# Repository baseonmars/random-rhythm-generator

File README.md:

Random Rhythm Generator
=======================

KiCad project for a random rhythm generator. Original circuit design by Tom Richards.

KiCad project by Dan Cseko <dan@baseonmars.co.uk>

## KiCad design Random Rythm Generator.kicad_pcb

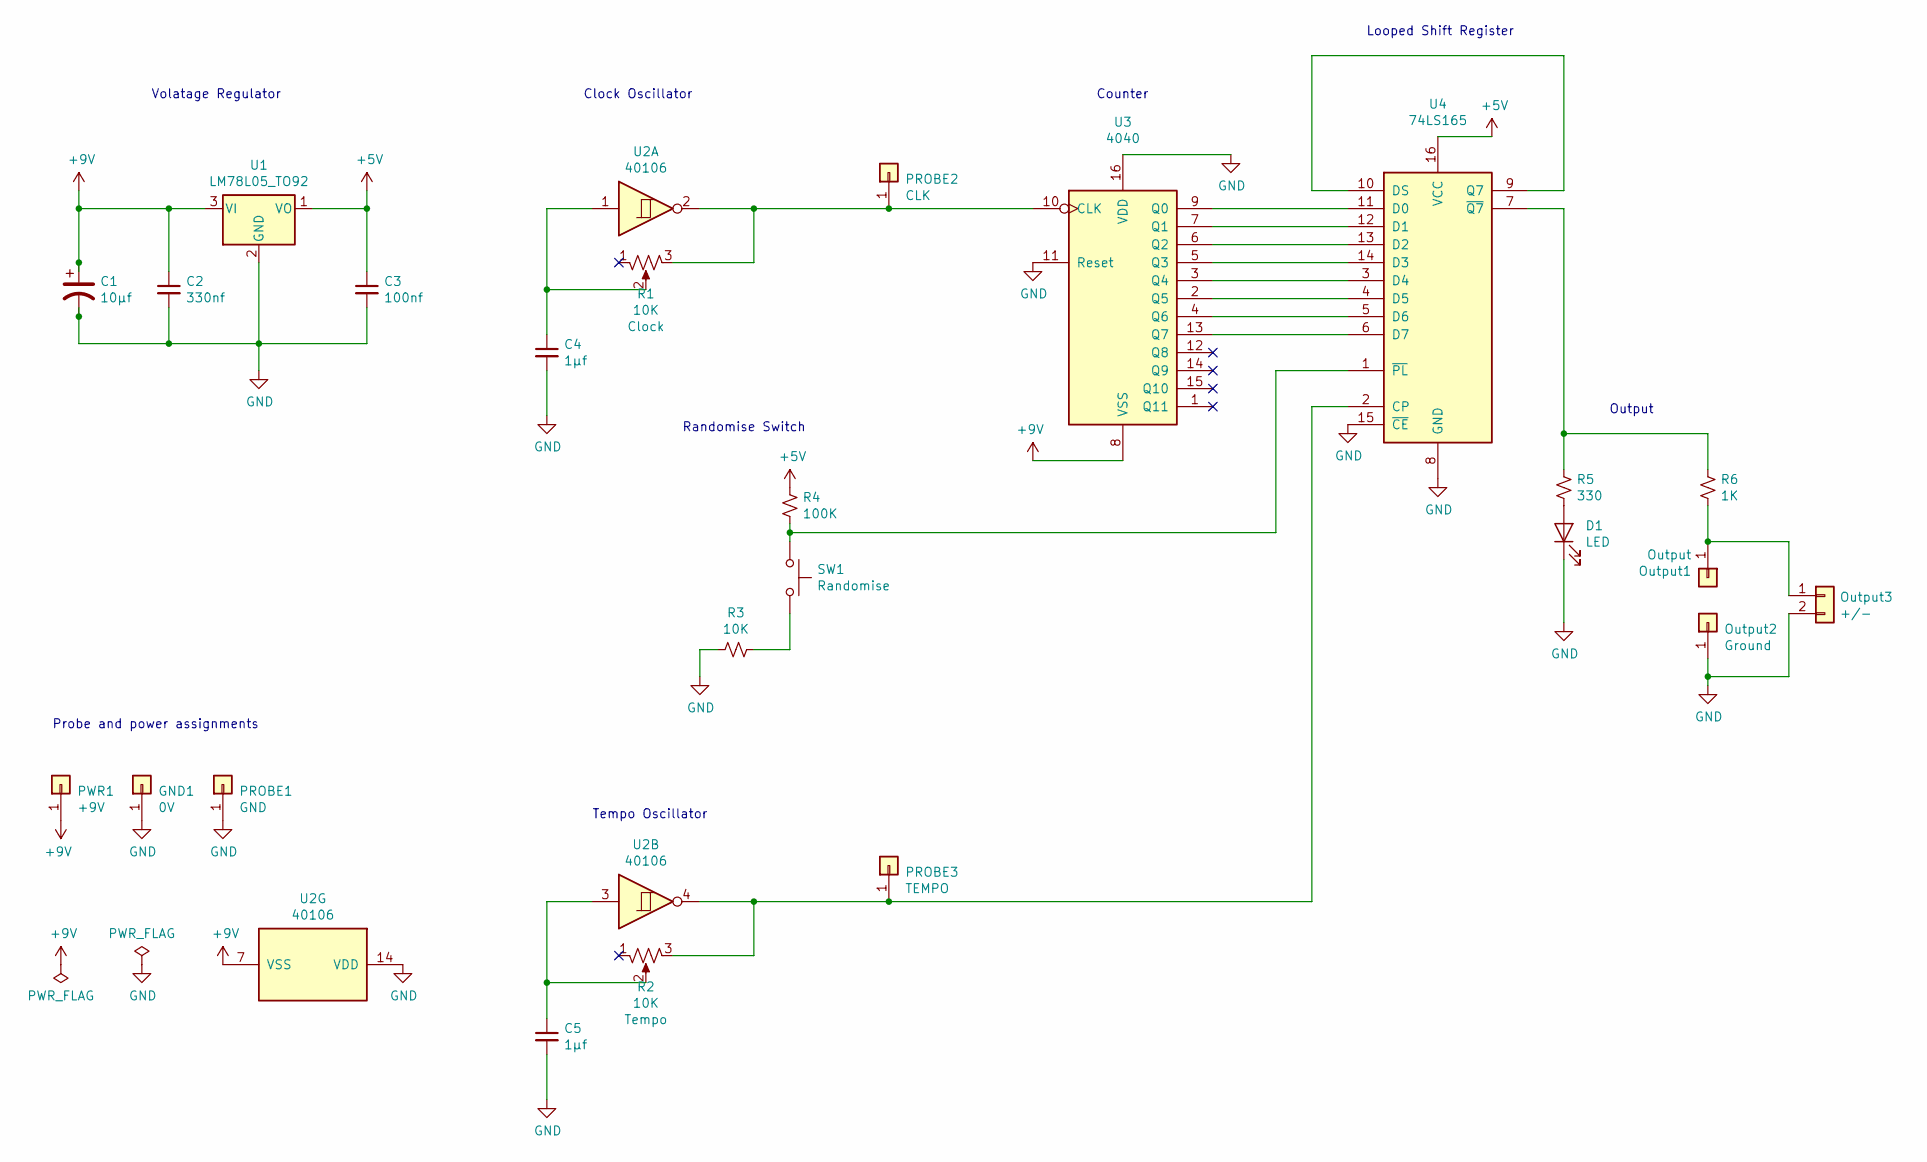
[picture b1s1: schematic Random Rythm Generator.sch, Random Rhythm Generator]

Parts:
C1: 10µf; C_Radial_D8.0mm_H7.0mm_P3.50mm
C2: 330nf; C_Disc_D5.0mm_W2.5mm_P5.00mm
C3: 100nf; C_Disc_D5.0mm_W2.5mm_P5.00mm
C4, C5: 1µf; C_Disc_D5.0mm_W2.5mm_P5.00mm
D1: LED; LED_D3.0mm
GND1: 0V; SolderWirePad_1x01_Drill0.8mm
Output1: Output; TestPoint_THTPad_2.5x2.5mm_Drill1.2mm
Output2: Ground; TestPoint_THTPad_2.5x2.5mm_Drill1.2mm
Output3: +/-; PinHeader_1x02_P2.54mm_Vertical
PROBE1: GND; TestPoint_Pad_2.5x2.5mm
PROBE2: CLK; TestPoint_Pad_2.5x2.5mm
PROBE3: TEMPO; TestPoint_Pad_2.5x2.5mm
PWR1: +9V; SolderWirePad_1x01_Drill0.8mm
R1, R2: 10K; Potentiometer_Bourns_3386P_Vertical
R3: 10K; R_Axial_DIN0207_L6.3mm_D2.5mm_P7.62mm_Horizontal
R4: 100K; R_Axial_DIN0207_L6.3mm_D2.5mm_P7.62mm_Horizontal
R5: 330; R_Axial_DIN0207_L6.3mm_D2.5mm_P7.62mm_Horizontal
R6: 1K; R_Axial_DIN0207_L6.3mm_D2.5mm_P7.62mm_Horizontal
SW1: Randomise; SW_PUSH_6mm_H9.5mm
U1: LM78L05_TO92; TO-92_Inline
U2: 40106; DIP-14_W7.62mm
U3: 4040; DIP-16_W7.62mm
U4: 74LS165; DIP-16_W7.62mm

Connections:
+5V: C3.1, R4.1, U1.1 (VO), U4.16 (VCC)
+9V: C1.1, C2.1, PWR1.1, U1.3 (VI), U2.7 (VSS), U3.8 (VSS)
GND: C1.2, C2.2, C3.2, C4.2, C5.2, D1.1 (K), GND1.1, Output2.1, Output3.2, PROBE1.1, R3.2, U1.2 (GND), U2.14 (VDD), U3.11 (Reset), U3.16 (VDD), U4.8 (GND), U4.15 (~CE)
unnamed: C4.1, R1.2, U2.1
unnamed: C5.1, R2.2, U2.3
unnamed: D1.2 (A), R5.2
unnamed: Output1.1, Output3.1, R6.2
unnamed: PROBE2.1, R1.3, U2.2, U3.10 (CLK)
unnamed: PROBE3.1, R2.3, U2.4, U4.2 (CP)
unnamed: R3.1, SW1.2
unnamed: R4.2, SW1.1, U4.1 (~PL)
unnamed: R5.1, R6.1, U4.7 (~Q7)
unnamed: U3.2 (Q5), U4.4 (D5)
unnamed: U3.3 (Q4), U4.3 (D4)
unnamed: U3.4 (Q6), U4.5 (D6)
unnamed: U3.5 (Q3), U4.14 (D3)
unnamed: U3.6 (Q2), U4.13 (D2)
unnamed: U3.7 (Q1), U4.12 (D1)
unnamed: U3.9 (Q0), U4.11 (D0)
unnamed: U3.13 (Q7), U4.6 (D7)
unnamed: U4.9 (Q7), U4.10 (DS)

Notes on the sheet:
Tempo Oscillator
Clock Oscillator
Volatage Regulator
Counter
Looped Shift Register
Probe and power assignments
Randomise Switch
Output

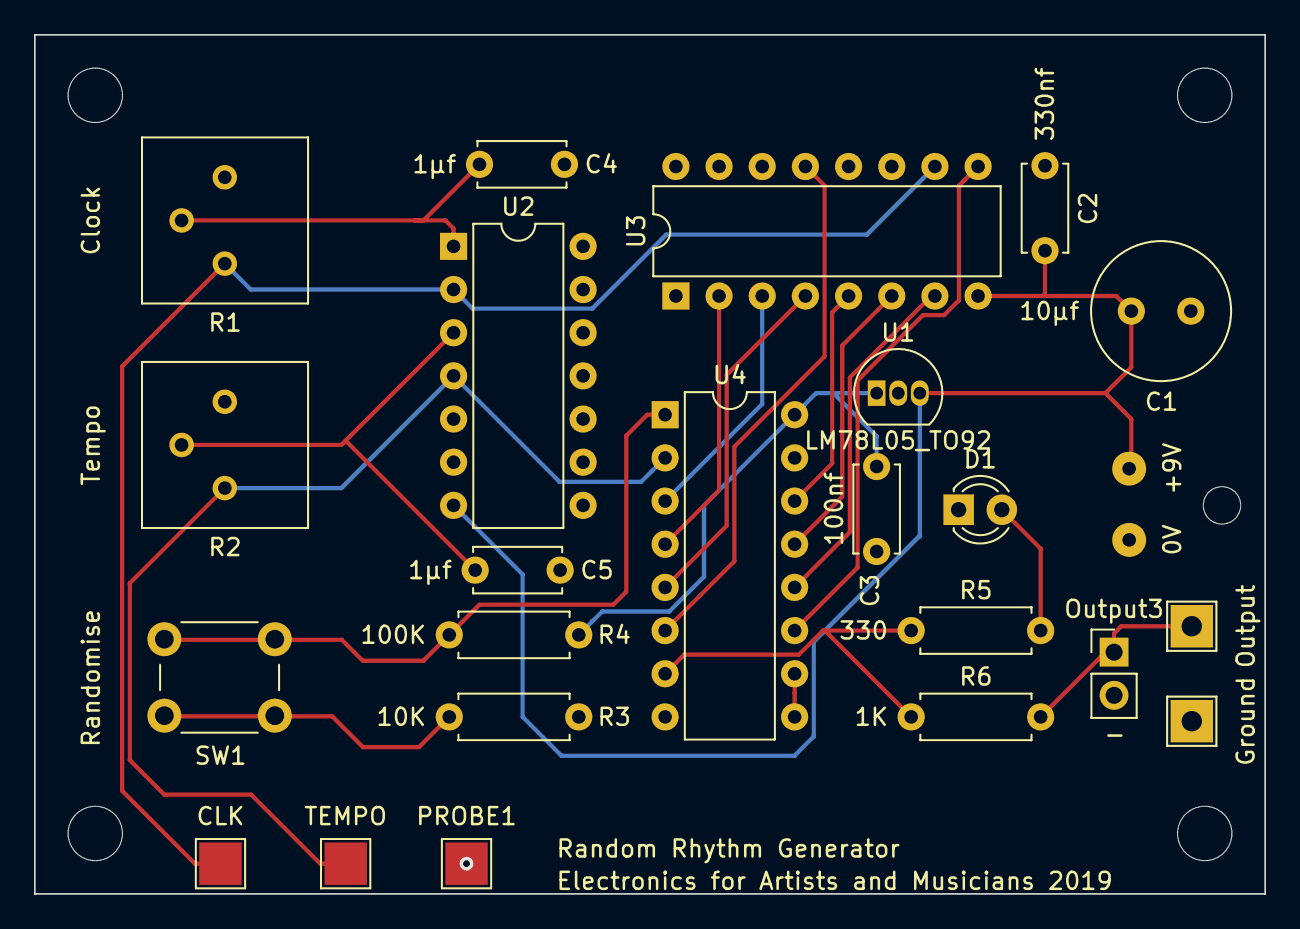
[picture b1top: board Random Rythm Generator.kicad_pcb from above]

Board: 2 copper layers, 72.4 x 50.5 mm, 25 parts (0 on the bottom side), 21 nets.

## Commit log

2019-07-06 Update README.md
    add images to readme.
2019-07-06 add smoothing capacitor to power supply
2019-07-06 neaten schematic and pcb layout slightly
2019-07-06 ignore bak files
2019-07-06 update netlist
2019-07-06 minor PCB and schematic tweaks
2019-07-06 move decoupling capacitors closer to ICs
2019-07-06 remove nested folder structure
2019-07-06 remove fp-info-cache
2019-07-08 add output pins
2019-07-08 fix chip power supply by swapping vdd and vss
